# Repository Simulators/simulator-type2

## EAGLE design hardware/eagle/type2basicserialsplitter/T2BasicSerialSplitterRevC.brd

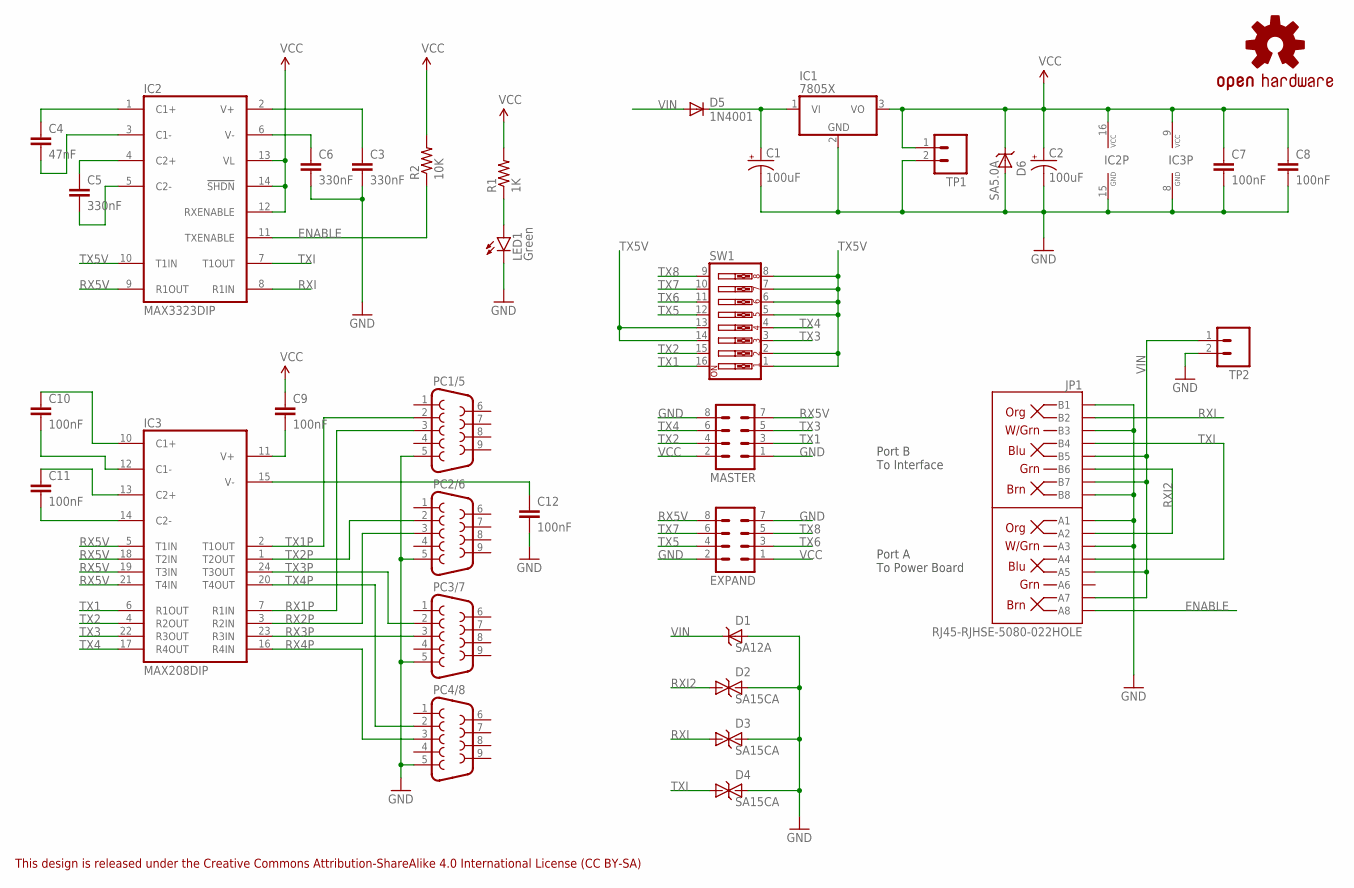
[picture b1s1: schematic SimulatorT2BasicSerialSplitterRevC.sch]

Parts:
C1, C2: 100uF; CPOL-RADIAL-100UF-25V
C3, C5, C6: 330nF; CAP-PTH-SMALL
C4: 47nF; CAP-PTH-SMALL
C7, C8, C9, C10, C11, C12: 100nF; CAP-PTH-SMALL
D1: SA12A; DO41_TVS_UNI
D2, D3, D4: SA15CA; DO41_TVS_BI
D5: 1N4001; DO41_DIODE
D6: SA5.0A; DO41_TVS_UNI
EXPAND: M04X2POL; 2X4-POLARISED
IC1: 7805X; TO220H
IC2: MAX3323DIP; DIL16
IC3: MAX208DIP; DIL24
JP1: RJ45-RJHSE-5080-022HOLE; RJ45-RJHSE-5080-02
LED1: Green; LED3MM_LARGEHOLES
LOGO1: OSHW-LOGOS; OSHW-LOGO-S
MASTER: M04X2POL; 2X4-POLARISED
PC1/5, PC2/6, PC3/7, PC4/8: DB9-CONNECTOR-PCBFEMALE; MULTICOMP-DB9-FEMALE-PCB-90DEG
R1: 1K; AXIAL-0.4
R2: 10K; AXIAL-0.4
SW1: SW_DIP-8; DIPSWITCH-08
TP1, TP2: M02PTH; 1X02

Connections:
ENABLE: IC2.11 (TXENABLE), JP1.A8, R2.P$1 (1)
GND: C1.2 (-), C2.2 (-), C3.2, C6.2, C7.2, C8.2, C12.2, D1.ANODE, D2.C, D3.C, D4.C, D6.ANODE, EXPAND.2, EXPAND.7, IC1.2 (GND), IC2.15 (GND), IC3.8 (GND), JP1.A1, JP1.A3, JP1.B1, JP1.B3, JP1.B8, LED1.K (C), MASTER.1, MASTER.8, PC1/5.5, PC2/6.5, PC3/7.5, PC4/8.5, TP1.2, TP2.2
unnamed: C3.1, IC2.2 (V+)
unnamed: C6.1, IC2.6 (V-)
unnamed: C5.1, IC2.4 (C2+)
unnamed: C5.2, IC2.5 (C2-)
unnamed: C4.1, IC2.1 (C1+)
unnamed: C4.2, IC2.3 (C1-)
unnamed: C11.2, IC3.14 (C2-)
unnamed: C11.1, IC3.13 (C2+)
unnamed: C10.1, IC3.10 (C1+)
unnamed: C10.2, IC3.12 (C1-)
unnamed: C12.1, IC3.15 (V-)
unnamed: C9.2, IC3.11 (V+)
POWER_LED: LED1.A, R1.P$1 (1)
RX1P: IC3.7 (R1IN), PC1/5.3
RX2P: IC3.3 (R2IN), PC2/6.3
RX3P: IC3.23 (R3IN), PC3/7.3
RX4P: IC3.16 (R4IN), PC4/8.3
RX5V: EXPAND.8, IC2.9 (R1OUT), IC3.5 (T1IN), IC3.18 (T2IN), IC3.19 (T3IN), IC3.21 (T4IN), MASTER.7
RXI: D3.A, IC2.8 (R1IN), JP1.B2
RXI2: D2.A, JP1.A2, JP1.B6
TX1: IC3.6 (R1OUT), MASTER.3, SW1.16
TX1P: IC3.2 (T1OUT), PC1/5.2
TX2: IC3.4 (R2OUT), MASTER.4, SW1.15
TX2P: IC3.1 (T2OUT), PC2/6.2
TX3: IC3.22 (R3OUT), MASTER.5, SW1.3
TX3P: IC3.24 (T3OUT), PC3/7.2
TX4: IC3.17 (R4OUT), MASTER.6, SW1.4
TX4P: IC3.20 (T4OUT), PC4/8.2
TX5: EXPAND.4, SW1.12
TX5V: IC2.10 (T1IN), SW1.1, SW1.2, SW1.5, SW1.6, SW1.7, SW1.8, SW1.13, SW1.14
TX6: EXPAND.3, SW1.11
TX7: EXPAND.6, SW1.10
TX8: EXPAND.5, SW1.9
TXI: D4.A, IC2.7 (T1OUT), JP1.A4, JP1.B4
VCC: C2.1 (+), C7.1, C8.1, C9.1, D6.CATHODE, EXPAND.1, IC1.3 (VO), IC2.12 (RXENABLE), IC2.13 (VL), IC2.14 (!SHDN), IC2.16 (VCC), IC3.9 (VCC), MASTER.2, R1.P$2 (2), R2.P$2 (2), TP1.1
VIN: D1.CATHODE, D5.A, JP1.A5, JP1.A7, JP1.B5, JP1.B7, TP2.1
VREG_IN: C1.1 (+), D5.C, IC1.1 (VI)

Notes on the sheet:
This design is released under the Creative Commons Attribution-ShareAlike 4.0 International License (CC BY-SA)
Port A To Power Board
Port B To Interface

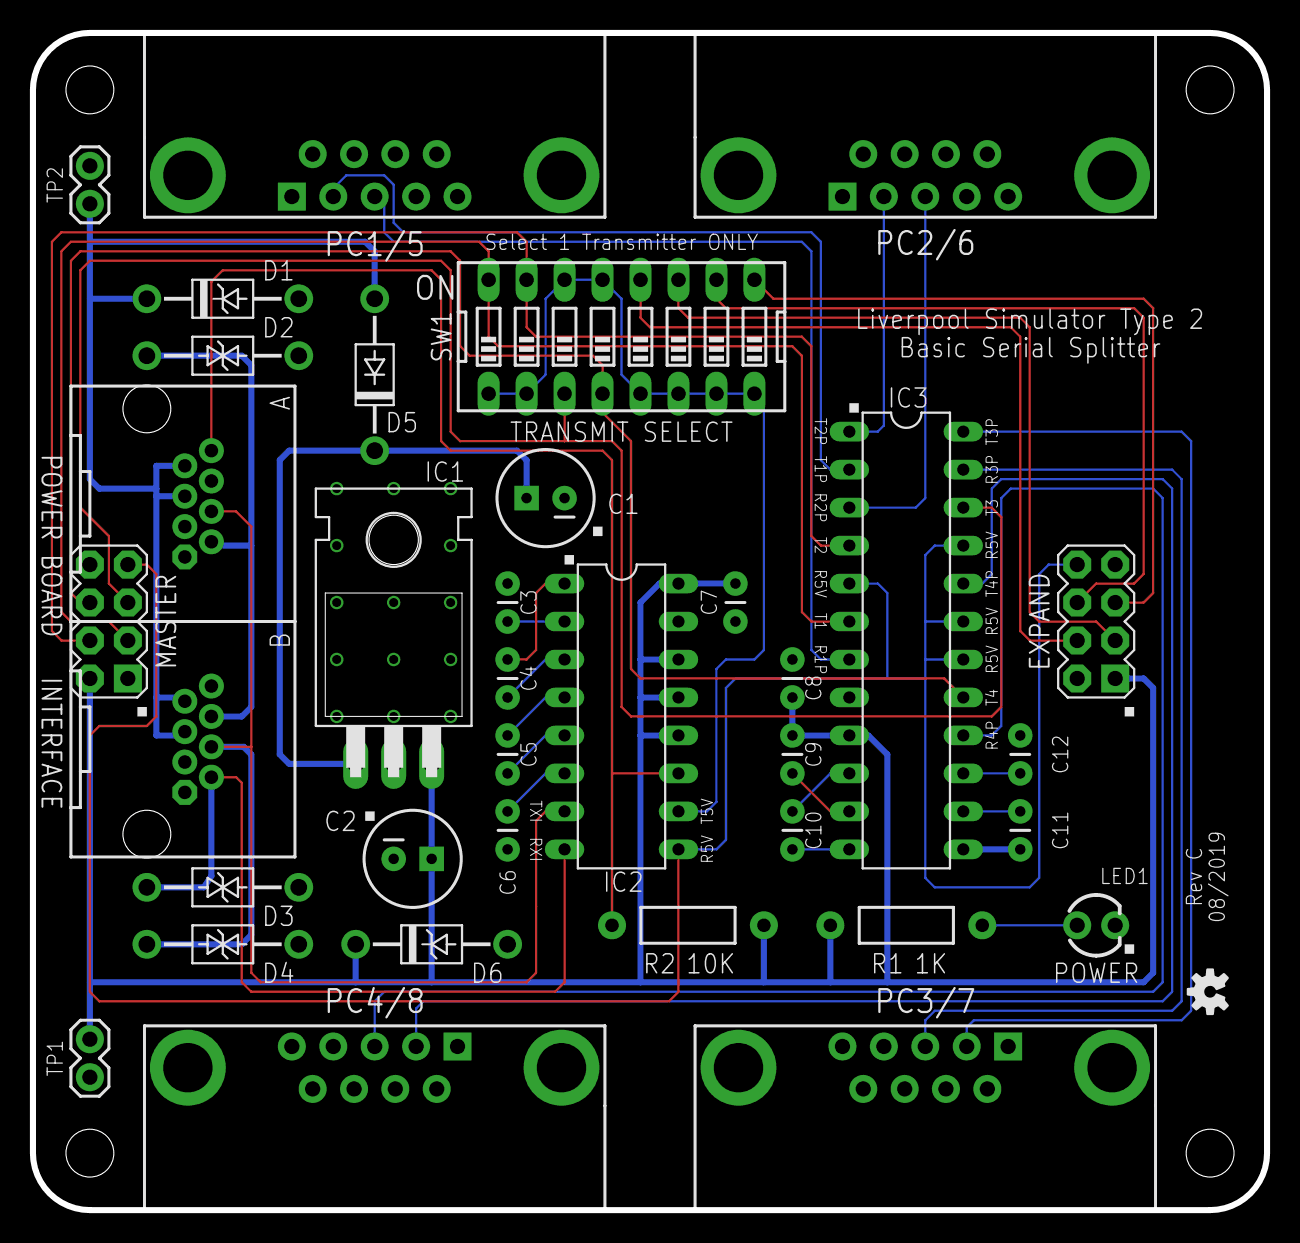
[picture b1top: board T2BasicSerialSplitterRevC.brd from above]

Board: 2 copper layers, 82.5 x 78.7 mm, 35 parts (0 on the bottom side), 39 nets.

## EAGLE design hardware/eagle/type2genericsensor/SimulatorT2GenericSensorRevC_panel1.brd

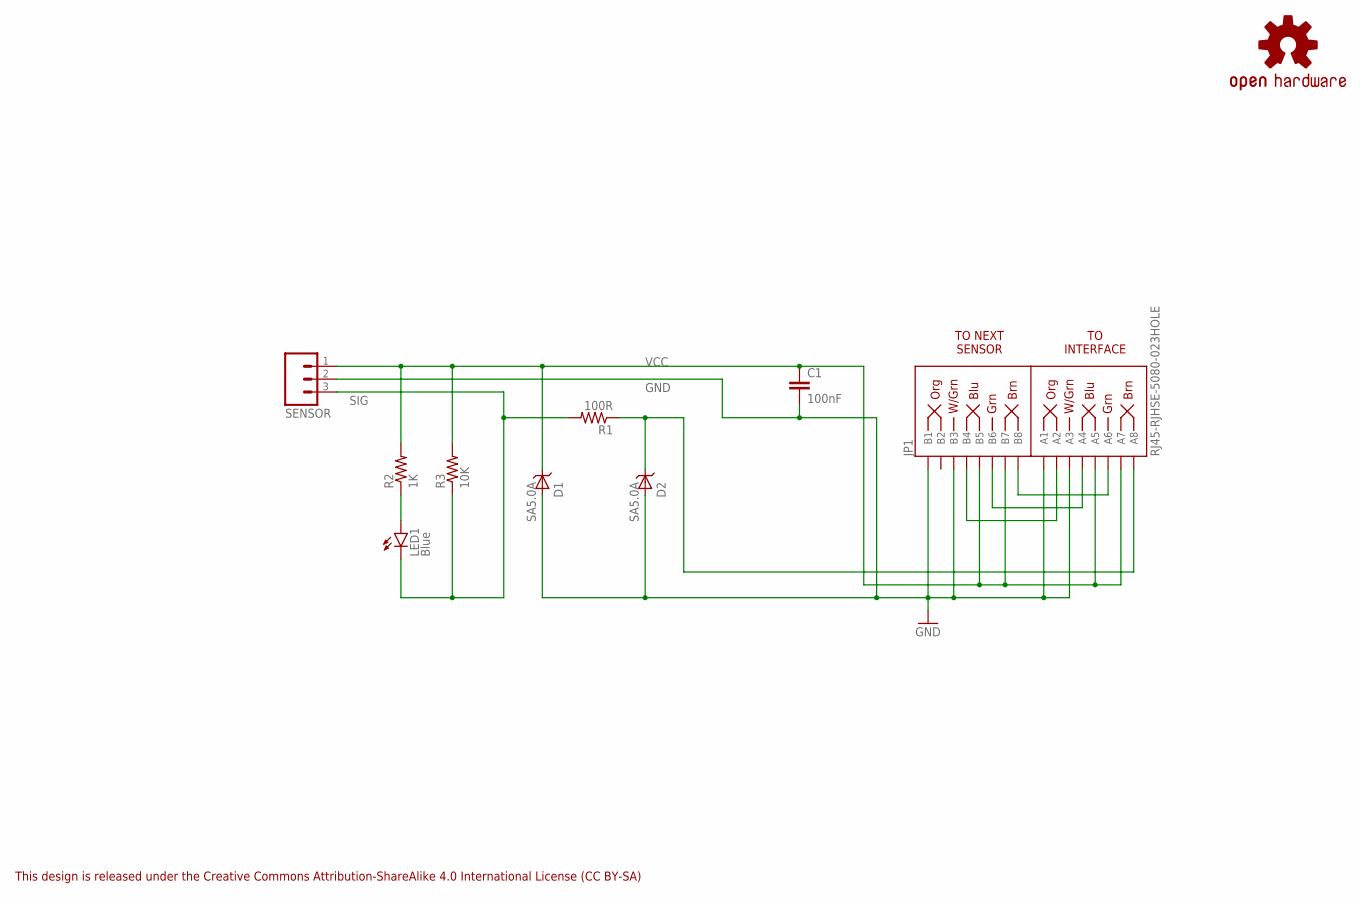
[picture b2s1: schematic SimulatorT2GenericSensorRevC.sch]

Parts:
C1: 100nF; CAP-PTH-SMALL
D1, D2: SA5.0A; DO41_TVS_UNI
JP1: RJ45-RJHSE-5080-023HOLE; RJ45-RJHSE-5080-02-3HOLE
LED1: Blue; LED3MM
LOGO1: OSHW-LOGOS; OSHW-LOGO-S
R1: 100R; AXIAL-0.4
R2: 1K; AXIAL-0.4
R3: 10K; AXIAL-0.4
SENSOR: M03PTH; 1X03

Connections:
!OUT!: D2.CATHODE, JP1.A8, R1.P$1 (1)
B2: JP1.A6, JP1.B8
B3: JP1.A4, JP1.B6
B4: JP1.A2, JP1.B4
GND: C1.2, D1.ANODE, D2.ANODE, JP1.A1, JP1.A3, JP1.B1, JP1.B3, SENSOR.2
LED: LED1.A, R2.P$1 (1)
SIG: LED1.K (C), R1.P$2 (2), R3.P$1 (1), SENSOR.3
VCC: C1.1, D1.CATHODE, JP1.A5, JP1.A7, JP1.B5, JP1.B7, R2.P$2 (2), R3.P$2 (2), SENSOR.1

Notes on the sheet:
This design is released under the Creative Commons Attribution-ShareAlike 4.0 International License (CC BY-SA)
TO INTERFACE
TO NEXT SENSOR

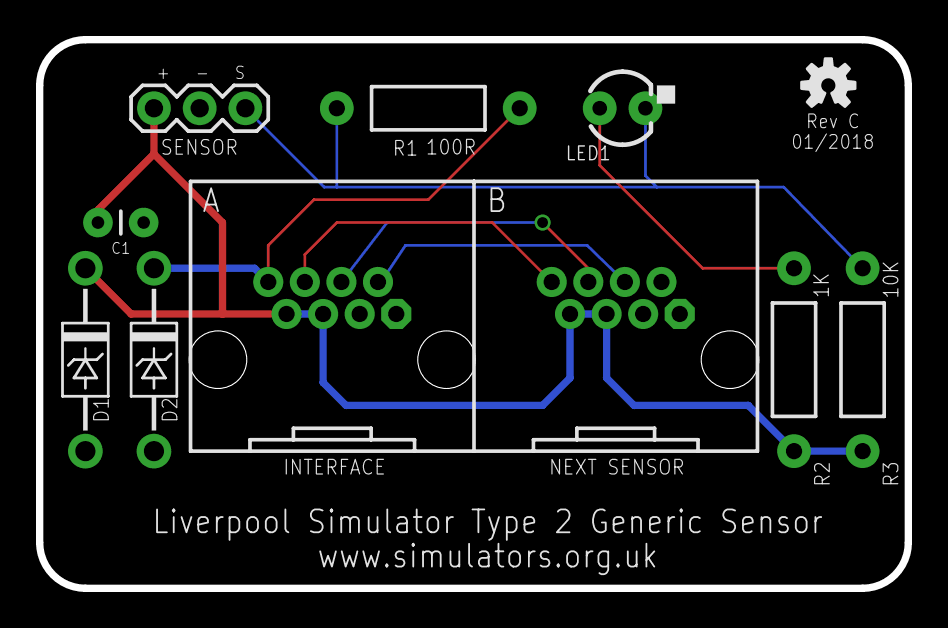
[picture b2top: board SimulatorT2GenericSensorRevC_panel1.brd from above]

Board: 2 copper layers, 48.3 x 30.5 mm, 11 parts (1 on the bottom side), 8 nets.

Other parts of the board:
E$1: WARNING_TRIANGLE_TPLACE

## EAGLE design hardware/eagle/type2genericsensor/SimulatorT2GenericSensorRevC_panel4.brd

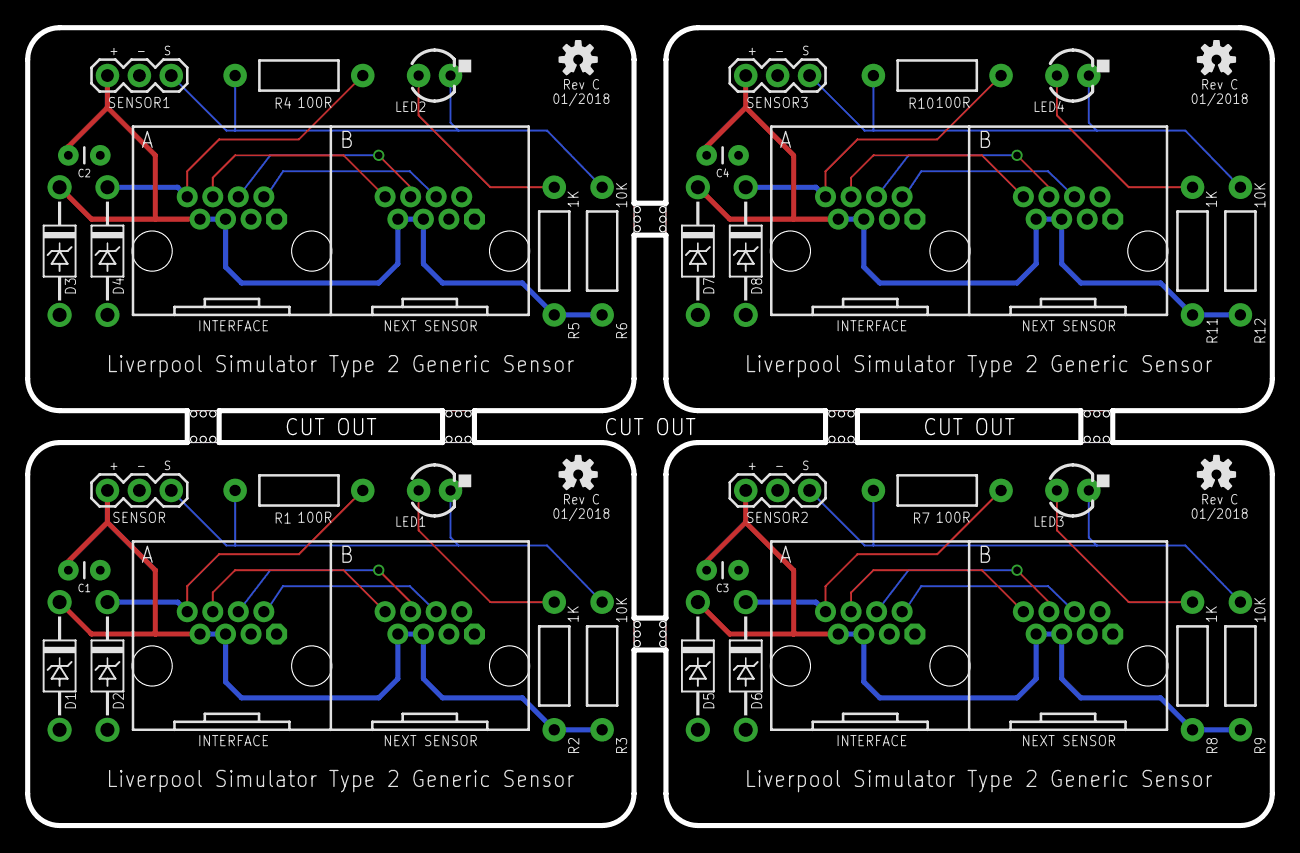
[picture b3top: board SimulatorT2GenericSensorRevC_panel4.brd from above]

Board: 2 copper layers, 99.1 x 63.5 mm, 46 parts (0 on the bottom side), 32 nets.

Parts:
C1, C2, C3, C4: 100nF; CAP-PTH-SMALL
D1, D2, D3, D4, D5, D6, D7, D8: SA5.0A; DO41_TVS_UNI
E$1, E$2, E$3, E$4, E$5, E$6: STAMP_HOLES
JP1, JP2, JP3, JP4: RJ45-RJHSE-5080-023HOLE; RJ45-RJHSE-5080-02-3HOLE
LED1, LED2, LED3, LED4: Blue; LED3MM
LOGO1, LOGO2, LOGO3, LOGO4: OSHW-LOGOS; OSHW-LOGO-S
R1, R4, R7, R10: 100R; AXIAL-0.4
R2, R5, R8, R11: 1K; AXIAL-0.4
R3, R6, R9, R12: 10K; AXIAL-0.4
SENSOR, SENSOR1, SENSOR2, SENSOR3: 1X03

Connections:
!OUT!: D2.CATHODE, JP1.A8, R1.P$1
!OUT!1: D4.CATHODE, JP2.A8, R4.P$1
!OUT!2: D6.CATHODE, JP3.A8, R7.P$1
!OUT!3: D8.CATHODE, JP4.A8, R10.P$1
B1: JP2.A6, JP2.B8
B2: JP1.A6, JP1.B8
B3: JP1.A4, JP1.B6
B4: JP1.A2, JP1.B4
B5: JP2.A4, JP2.B6
B6: JP2.A2, JP2.B4
B7: JP3.A6, JP3.B8
B8: JP3.A4, JP3.B6
B9: JP3.A2, JP3.B4
B10: JP4.A6, JP4.B8
B11: JP4.A4, JP4.B6
B12: JP4.A2, JP4.B4
GND: C1.2, D1.ANODE, D2.ANODE, JP1.A1, JP1.A3, JP1.B1, JP1.B3, SENSOR.2
GND1: C2.2, D3.ANODE, D4.ANODE, JP2.A1, JP2.A3, JP2.B1, JP2.B3, SENSOR1.2
GND2: C3.2, D5.ANODE, D6.ANODE, JP3.A1, JP3.A3, JP3.B1, JP3.B3, SENSOR2.2
GND3: C4.2, D7.ANODE, D8.ANODE, JP4.A1, JP4.A3, JP4.B1, JP4.B3, SENSOR3.2
LED: LED1.A, R2.P$1
LED1: LED2.A, R5.P$1
LED2: LED3.A, R8.P$1
LED3: LED4.A, R11.P$1
SIG: LED1.K, R1.P$2, R3.P$1, SENSOR.3
SIG1: LED2.K, R4.P$2, R6.P$1, SENSOR1.3
SIG2: LED3.K, R7.P$2, R9.P$1, SENSOR2.3
SIG3: LED4.K, R10.P$2, R12.P$1, SENSOR3.3
VCC: C1.1, D1.CATHODE, JP1.A5, JP1.A7, JP1.B5, JP1.B7, R2.P$2, R3.P$2, SENSOR.1
VCC1: C2.1, D3.CATHODE, JP2.A5, JP2.A7, JP2.B5, JP2.B7, R5.P$2, R6.P$2, SENSOR1.1
VCC2: C3.1, D5.CATHODE, JP3.A5, JP3.A7, JP3.B5, JP3.B7, R8.P$2, R9.P$2, SENSOR2.1
VCC3: C4.1, D7.CATHODE, JP4.A5, JP4.A7, JP4.B5, JP4.B7, R11.P$2, R12.P$2, SENSOR3.1

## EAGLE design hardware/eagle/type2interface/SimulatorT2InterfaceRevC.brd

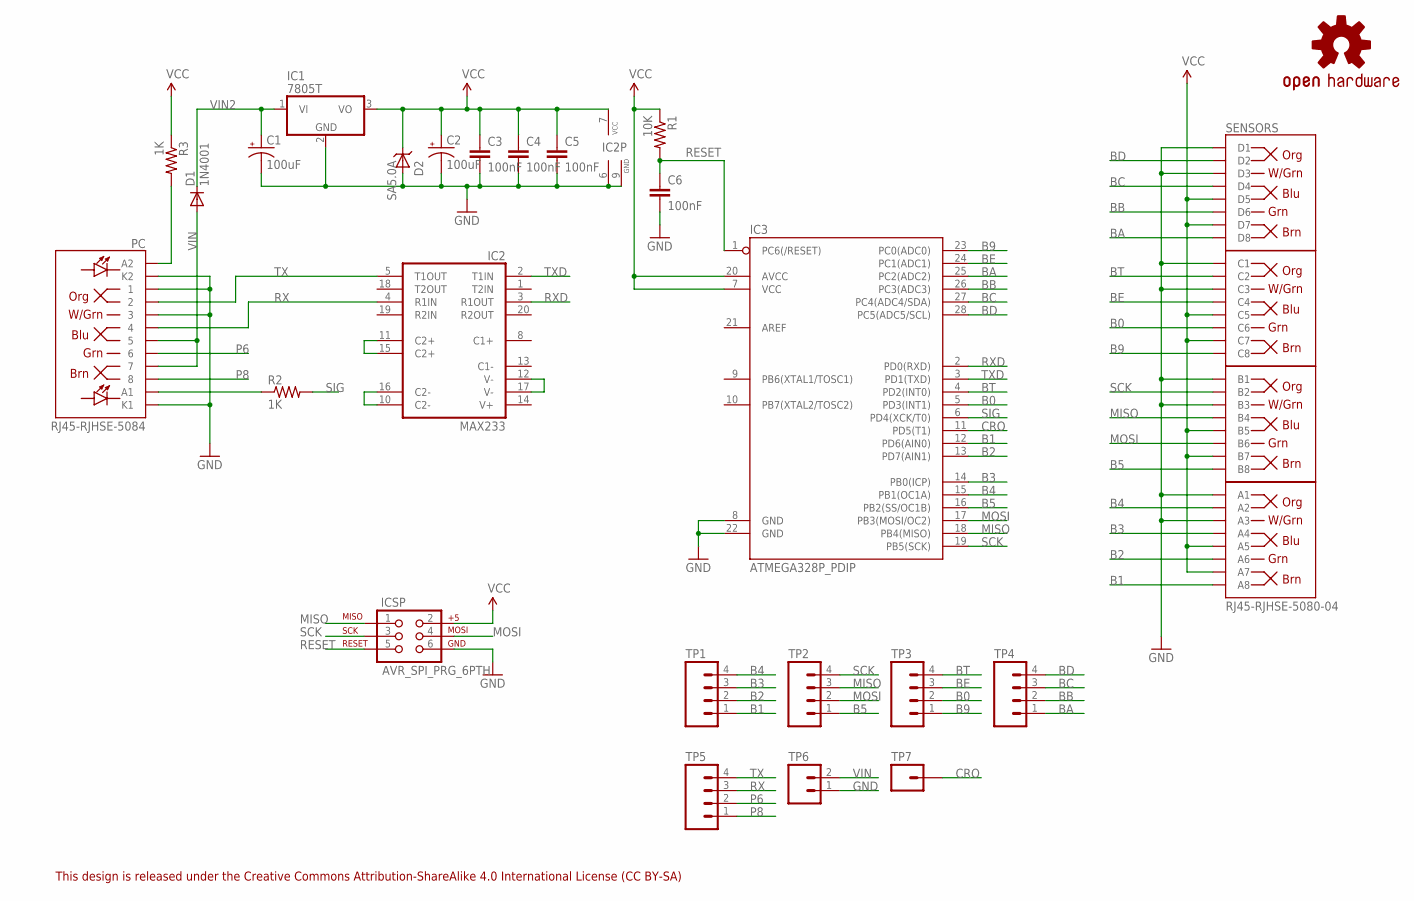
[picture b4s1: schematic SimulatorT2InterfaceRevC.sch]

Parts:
C1, C2: 100uF; CPOL-RADIAL-100UF-25V
C3, C4, C5, C6: 100nF; CAP-PTH-SMALL
D1: 1N4001; DO41_DIODE
D2: SA5.0A; DO41_TVS_UNI
IC1: 7805T; TO220H
IC2: MAX233; DIL20
IC3: ATMEGA328P_PDIP; DIL28-3
ICSP: AVR_SPI_PRG_6PTH; 2X3
LOGO1: OSHW-LOGOS; OSHW-LOGO-S
PC: RJ45-RJHSE-5084
R1: 10K; AXIAL-0.4
R2, R3: 1K; AXIAL-0.4
SENSORS: RJ45-RJHSE-5080-04
TP1, TP2, TP3, TP4, TP5: M04PTH; 1X04
TP6: M02PTH; 1X02
TP7: M01PTH; 1X01

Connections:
B0: IC3.5 (PD3(INT1)), SENSORS.C6, TP3.2
B1: IC3.12 (PD6(AIN0)), SENSORS.A8, TP1.1
B2: IC3.13 (PD7(AIN1)), SENSORS.A6, TP1.2
B3: IC3.14 (PB0(ICP)), SENSORS.A4, TP1.3
B4: IC3.15 (PB1(OC1A)), SENSORS.A2, TP1.4
B5: IC3.16 (PB2(SS/OC1B)), SENSORS.B8, TP2.1
B9: IC3.23 (PC0(ADC0)), SENSORS.C8, TP3.1
BA: IC3.25 (PC2(ADC2)), SENSORS.D8, TP4.1
BB: IC3.26 (PC3(ADC3)), SENSORS.D6, TP4.2
BC: IC3.27 (PC4(ADC4/SDA)), SENSORS.D4, TP4.3
BD: IC3.28 (PC5(ADC5/SCL)), SENSORS.D2, TP4.4
BE: IC3.24 (PC1(ADC1)), SENSORS.C4, TP3.3
BT: IC3.4 (PD2(INT0)), SENSORS.C2, TP3.4
CRO: IC3.11 (PD5(T1)), TP7.1
GND: C1.2 (-), C2.2 (-), C3.2, C4.2, C5.2, C6.2, D2.ANODE, IC1.2 (GND), IC2.6 (GND), IC2.9 (GND), IC3.8 (GND), IC3.22 (GND), ICSP.6, PC.1, PC.3, PC.K1, PC.K2, SENSORS.A1, SENSORS.A3, SENSORS.B1, SENSORS.B3, SENSORS.C1, SENSORS.C3, SENSORS.D1, SENSORS.D3, TP6.1
LED1: PC.A1, R2.P$1 (1)
LED2: PC.A2, R3.P$2 (2)
MISO: IC3.18 (PB4(MISO)), ICSP.1, SENSORS.B4, TP2.3
MOSI: IC3.17 (PB3(MOSI/OC2)), ICSP.4, SENSORS.B6, TP2.2
unnamed: IC2.10 (C2-), IC2.16 (C2-)
unnamed: IC2.11 (C2+), IC2.15 (C2+)
unnamed: IC2.12 (V-), IC2.17 (V-)
P6: PC.6, TP5.2
P8: PC.8, TP5.1
RESET: C6.1, IC3.1 (PC6(/RESET)), ICSP.5, R1.P$2 (2)
RX: IC2.4 (R1IN), PC.4, TP5.3
RXD: IC2.3 (R1OUT), IC3.2 (PD0(RXD))
SCK: IC3.19 (PB5(SCK)), ICSP.3, SENSORS.B2, TP2.4
SIG: IC3.6 (PD4(XCK/T0)), R2.P$2 (2)
TX: IC2.5 (T1OUT), PC.2, TP5.4
TXD: IC2.2 (T1IN), IC3.3 (PD1(TXD))
VCC: C2.1 (+), C3.1, C4.1, C5.1, D2.CATHODE, IC1.3 (VO), IC2.7 (VCC), IC3.7 (VCC), IC3.20 (AVCC), ICSP.2, R1.P$1 (1), R3.P$1 (1), SENSORS.A5, SENSORS.A7, SENSORS.B5, SENSORS.B7, SENSORS.C5, SENSORS.C7, SENSORS.D5, SENSORS.D7
VIN: D1.A, PC.5, PC.7, TP6.2
VIN2: C1.1 (+), D1.C, IC1.1 (VI)

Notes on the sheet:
This design is released under the Creative Commons Attribution-ShareAlike 4.0 International License (CC BY-SA)

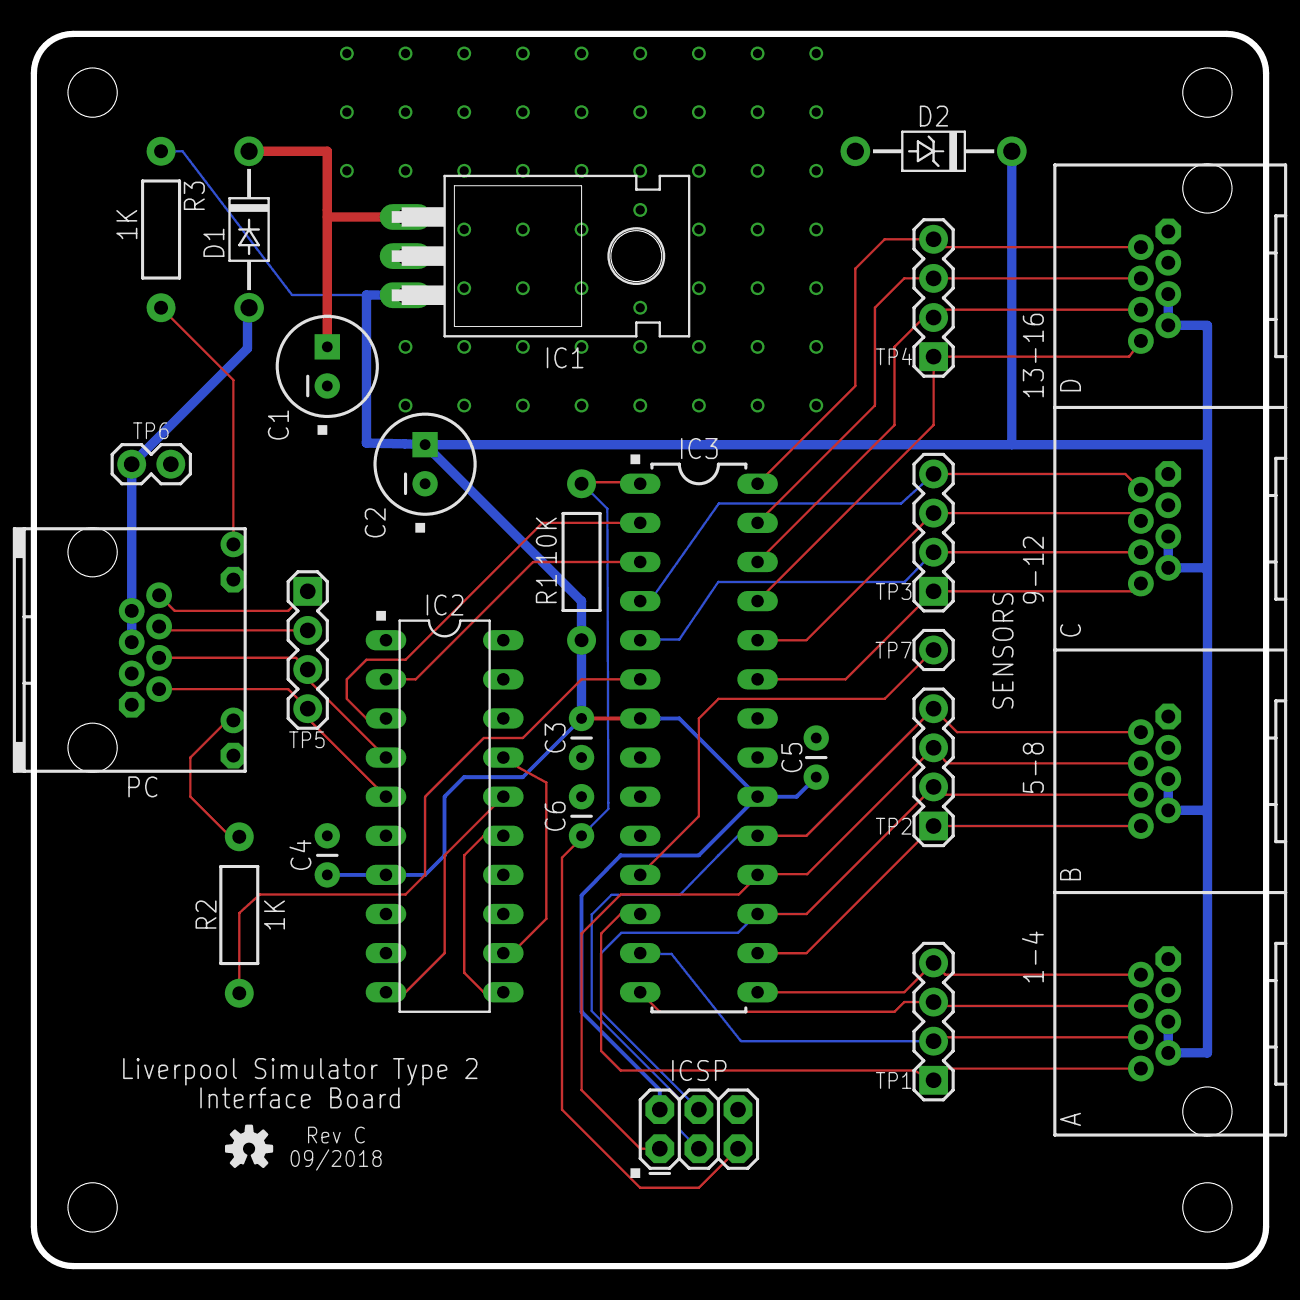
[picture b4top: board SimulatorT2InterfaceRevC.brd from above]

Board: 2 copper layers, 80.0 x 80.0 mm, 25 parts (0 on the bottom side), 34 nets.

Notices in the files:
parts and their libraries:
SparkFun-Aesthetics: Licensing: Creative Commons ShareAlike 4.0 International - https://creativecommons.org/licenses/by-sa/4.0
